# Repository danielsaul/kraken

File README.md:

The Kraken
==========
Poseidon Ocean Drifter Project  
http://poseidon.sgsphysics.co.uk

Tracker
http://track.poseidon.sgsphysics.co.uk/

Various Authors

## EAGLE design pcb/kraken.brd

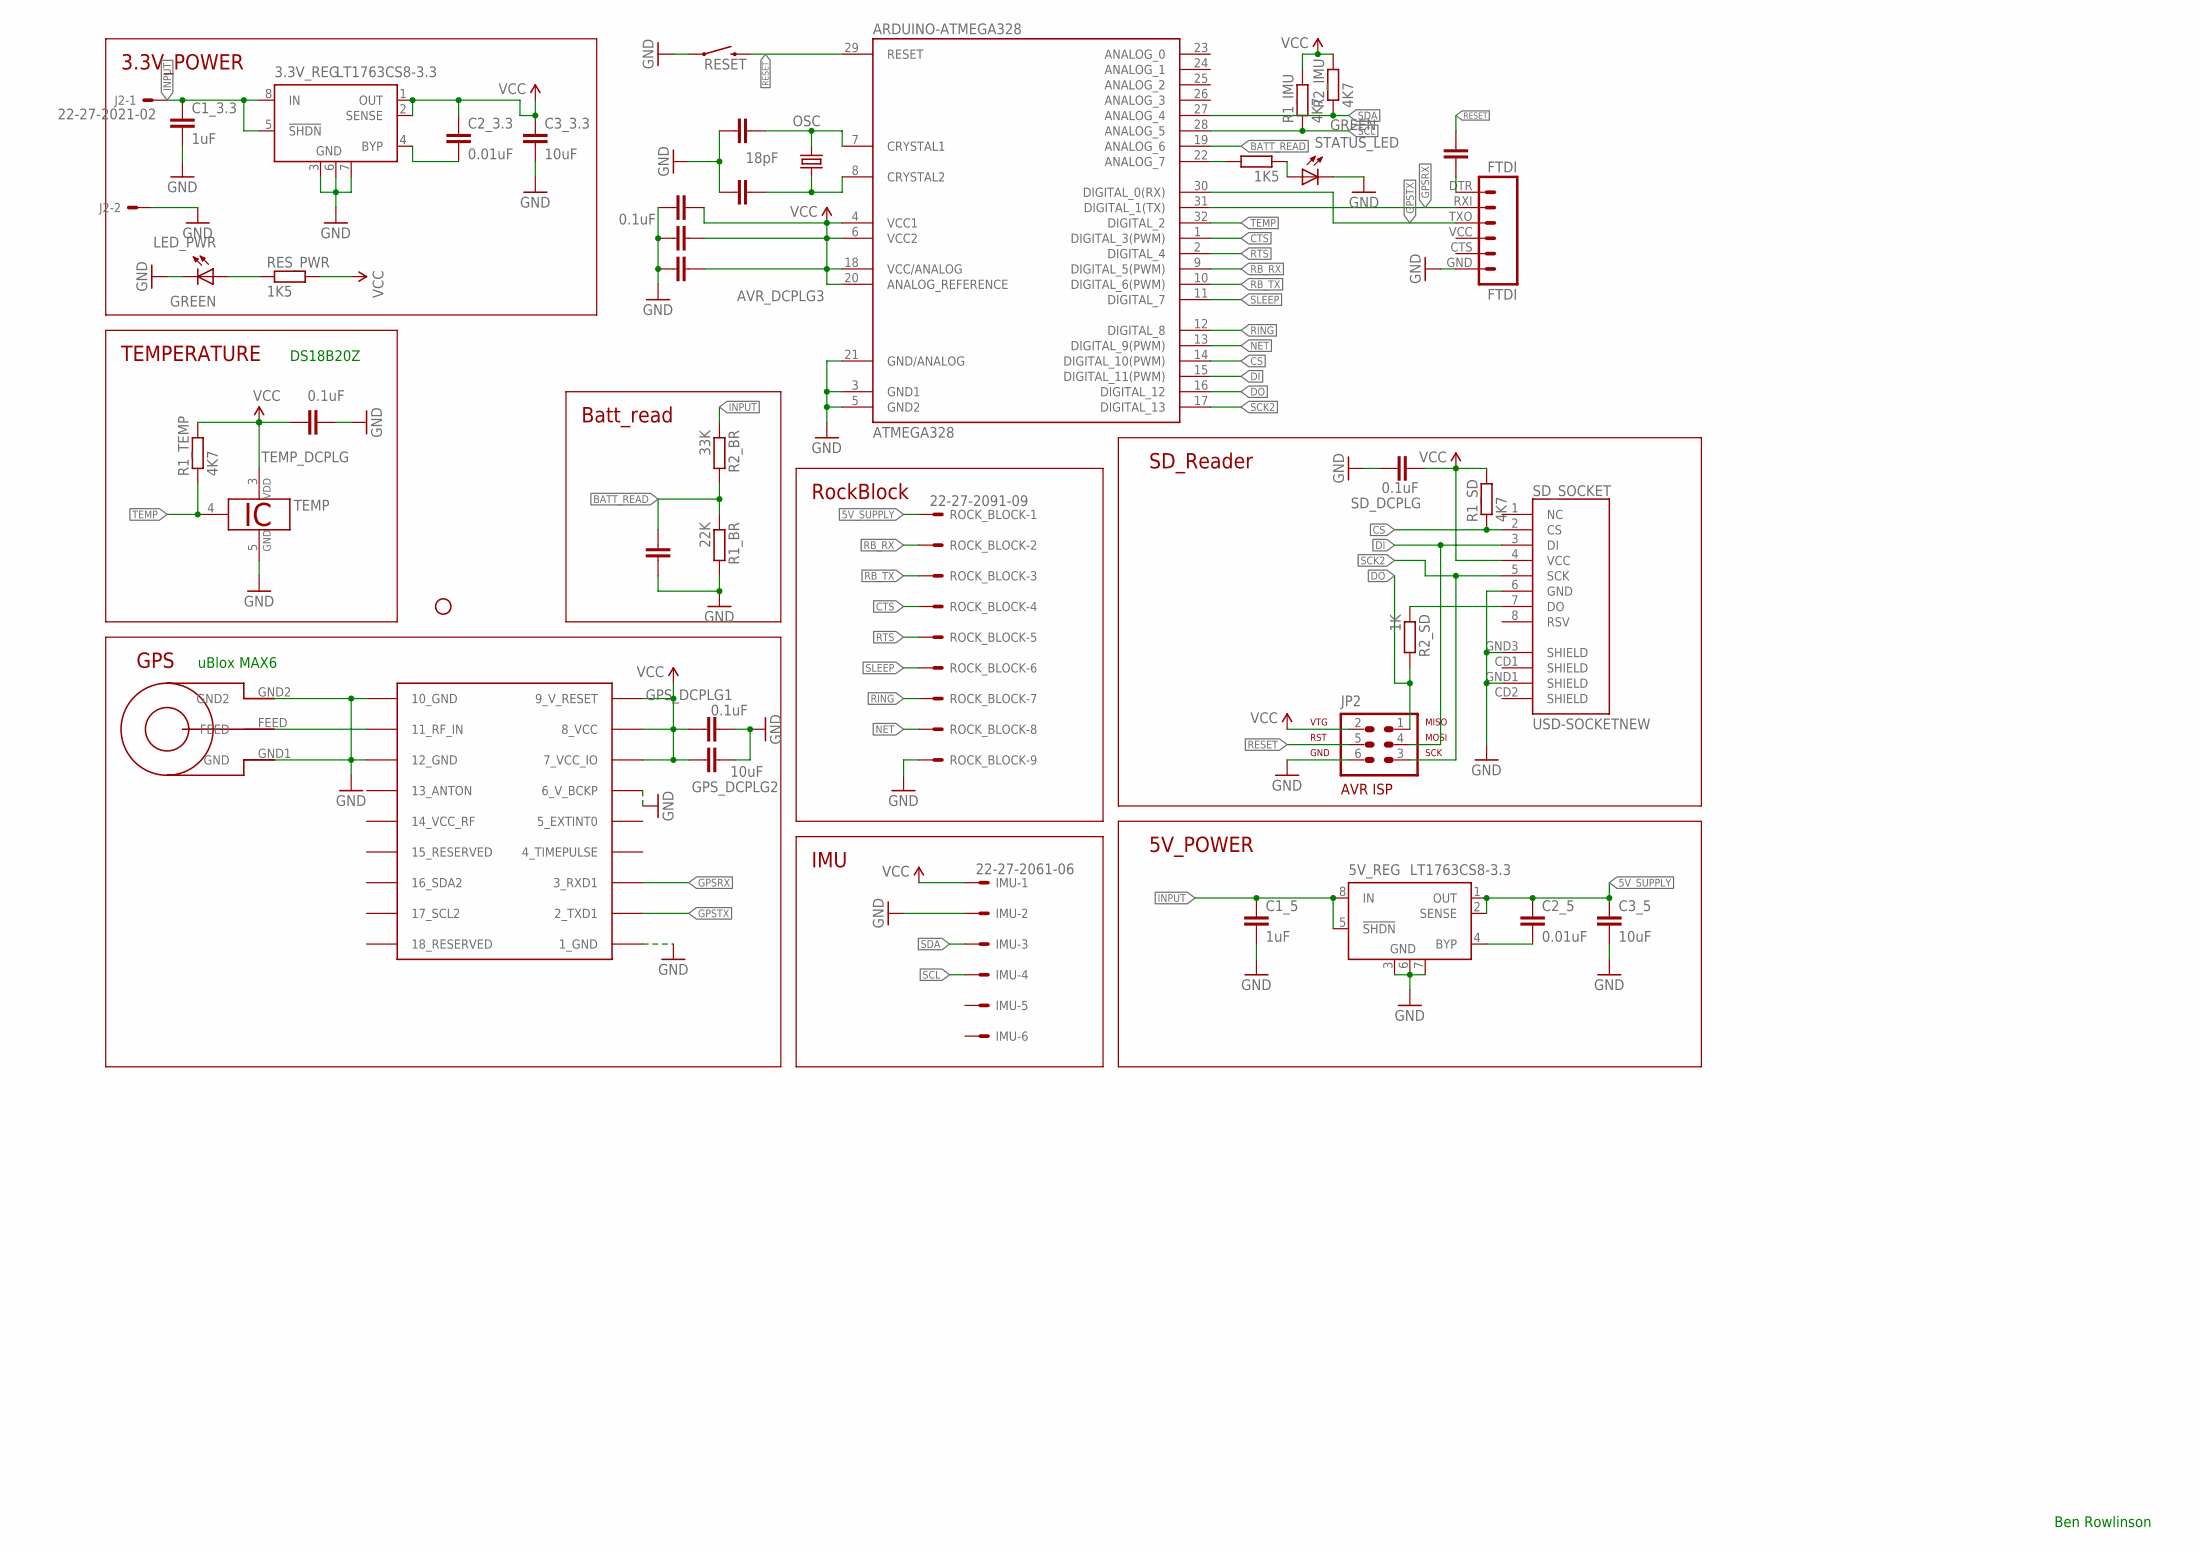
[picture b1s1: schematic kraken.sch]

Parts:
3.3V_REG, 5V_REG: LT1763CS8-3.3; SOIC8
ARDUINO-ATMEGA328: ATMEGA328; TQFP32-08
AVR_DCPLG1, AVR_DCPLG2, AVR_DCPLG3: 0.1uF; 0805
C1_3.3, C1_5: 1uF; 0805
C1_BR: 0.1uF; 0805
C1_OSC, C2_OSC: 18pF; 0805
C2_3.3, C2_5: 0.01uF; 0805
C3_3.3, C3_5: 10uF; 0805
FTDI: FTDI; FTDI_BASIC
FTDI_DCPLG: 0.1uF; 0805
GPS_DCPLG1: 0.1uF; 0805
GPS_DCPLG2: 10uF; 0805
IMU: 22-27-2061-06; 6410-06
J2: 22-27-2021-02; 6410-02
JP1: STAND-OFF
JP2: AVR-ISP-6
LED_PWR: GREEN; CHIPLED_0603
OSC: 16MHz; CRYSTAL-SMD-5X3
R1_BR: 22K; R0805
R1_IMU, R1_SD, R1_TEMP, R2_IMU: 4K7; R0805
R2_BR: 33K; R0805
R2_SD: 1K; R0805
RESET: SW-MOMENTARY-SMD; TACTILE-SWITCH-1101NE
RES_PWR: 1K5; R0805
ROCK_BLOCK: 22-27-2091-09; 6410-09
R_STATUS: 1K5; R0805
SD_DCPLG: 0.1uF; 0805
SD_SOCKET: USD-SOCKETNEW; MICRO-SD-SOCKET-PP
STATUS_LED: GREEN; CHIPLED_0603
TEMP: DS18B20Z; SO08
TEMP_DCPLG: 0.1uF; 0805
U$1: UBLOX_MAX-6
U$2: SARANTEL-SR1202

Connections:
5V_SUPPLY: 5V_REG.1 (OUT), 5V_REG.2 (SENSE), C2_5.1, C3_5.1, ROCK_BLOCK.1
BATT_READ: ARDUINO-ATMEGA328.19 (ANALOG_6), C1_BR.2, R1_BR.1, R2_BR.2
CS: ARDUINO-ATMEGA328.14 (DIGITAL_10(PWM)), R1_SD.1, SD_SOCKET.2 (CS)
CTS: ARDUINO-ATMEGA328.1 (DIGITAL_3(PWM)), ROCK_BLOCK.4
DI: ARDUINO-ATMEGA328.15 (DIGITAL_11(PWM)), JP2.4, SD_SOCKET.3 (DI)
DO: ARDUINO-ATMEGA328.16 (DIGITAL_12), JP2.1, R2_SD.2
GND: 3.3V_REG.3 (GND), 3.3V_REG.6 (GND), 3.3V_REG.7 (GND), 5V_REG.3 (GND), 5V_REG.6 (GND), 5V_REG.7 (GND), ARDUINO-ATMEGA328.3 (GND1), ARDUINO-ATMEGA328.5 (GND2), ARDUINO-ATMEGA328.21 (GND/ANALOG), AVR_DCPLG1.1, AVR_DCPLG2.1, AVR_DCPLG3.1, C1_3.3.2, C1_5.2, C1_BR.1, C1_OSC.1, C2_OSC.1, C3_3.3.2, C3_5.2, FTDI.GND (6), GPS_DCPLG1.2, GPS_DCPLG2.2, IMU.2, J2.2, JP2.6, LED_PWR.C, R1_BR.2, RESET.P$1 (1), ROCK_BLOCK.9, SD_DCPLG.2, SD_SOCKET.6 (GND), SD_SOCKET.GND1 (SHIELD), SD_SOCKET.GND3 (SHIELD), STATUS_LED.C, TEMP.5 (GND), TEMP_DCPLG.1, U$1.1_GND, U$1.6_V_BCKP, U$1.10_GND, U$1.12_GND, U$2.GND1 (GND), U$2.GND2
GPSRX: ARDUINO-ATMEGA328.31 (DIGITAL_1(TX)), FTDI.RXI (2), U$1.3_RXD1
GPSTX: ARDUINO-ATMEGA328.30 (DIGITAL_0(RX)), FTDI.TXO (3), U$1.2_TXD1
INPUT: 3.3V_REG.5 (!SHDN), 3.3V_REG.8 (IN), 5V_REG.5 (!SHDN), 5V_REG.8 (IN), C1_3.3.1, C1_5.1, J2.1, R2_BR.1
unnamed: R_STATUS.1, STATUS_LED.A
unnamed: R2_SD.1, SD_SOCKET.7 (DO)
unnamed: LED_PWR.A, RES_PWR.1
unnamed: ARDUINO-ATMEGA328.22 (ANALOG_7), R_STATUS.2
unnamed: ARDUINO-ATMEGA328.8 (CRYSTAL2), C2_OSC.2, OSC.1
unnamed: ARDUINO-ATMEGA328.7 (CRYSTAL1), C1_OSC.2, OSC.3 (2)
unnamed: 3.3V_REG.4 (BYP), C2_3.3.2
unnamed: U$1.11_RF_IN, U$2.FEED
unnamed: 5V_REG.4 (BYP), C2_5.2
unnamed: FTDI.DTR (1), FTDI_DCPLG.2
NET: ARDUINO-ATMEGA328.13 (DIGITAL_9(PWM)), ROCK_BLOCK.8
RB_RX: ARDUINO-ATMEGA328.9 (DIGITAL_5(PWM)), ROCK_BLOCK.2
RB_TX: ARDUINO-ATMEGA328.10 (DIGITAL_6(PWM)), ROCK_BLOCK.3
RESET: ARDUINO-ATMEGA328.29 (RESET), FTDI_DCPLG.1, JP2.5, RESET.P$2 (2)
RING: ARDUINO-ATMEGA328.12 (DIGITAL_8), ROCK_BLOCK.7
RTS: ARDUINO-ATMEGA328.2 (DIGITAL_4), ROCK_BLOCK.5
SCK2: ARDUINO-ATMEGA328.17 (DIGITAL_13), JP2.3, SD_SOCKET.5 (SCK)
SCL: ARDUINO-ATMEGA328.28 (ANALOG_5), IMU.4, R1_IMU.1
SDA: ARDUINO-ATMEGA328.27 (ANALOG_4), IMU.3, R2_IMU.1
SLEEP: ARDUINO-ATMEGA328.11 (DIGITAL_7), ROCK_BLOCK.6
TEMP: ARDUINO-ATMEGA328.32 (DIGITAL_2), R1_TEMP.1, TEMP.4 (1W)
VCC: 3.3V_REG.1 (OUT), 3.3V_REG.2 (SENSE), ARDUINO-ATMEGA328.4 (VCC1), ARDUINO-ATMEGA328.6 (VCC2), ARDUINO-ATMEGA328.18 (VCC/ANALOG), ARDUINO-ATMEGA328.20 (ANALOG_REFERENCE), AVR_DCPLG1.2, AVR_DCPLG2.2, AVR_DCPLG3.2, C2_3.3.1, C3_3.3.1, GPS_DCPLG1.1, GPS_DCPLG2.1, IMU.1, JP2.2, R1_IMU.2, R1_SD.2, R1_TEMP.2, R2_IMU.2, RES_PWR.2, SD_DCPLG.1, SD_SOCKET.4 (VCC), TEMP.3 (VDD), TEMP_DCPLG.2, U$1.7_VCC_IO, U$1.8_VCC, U$1.9_V_RESET

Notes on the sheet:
3.3V_POWER
TEMPERATURE
Ben Rowlinson
GPS
uBlox MAX6
DS18B20Z
RockBlock
IMU
5V_POWER
SD_Reader
Batt_read

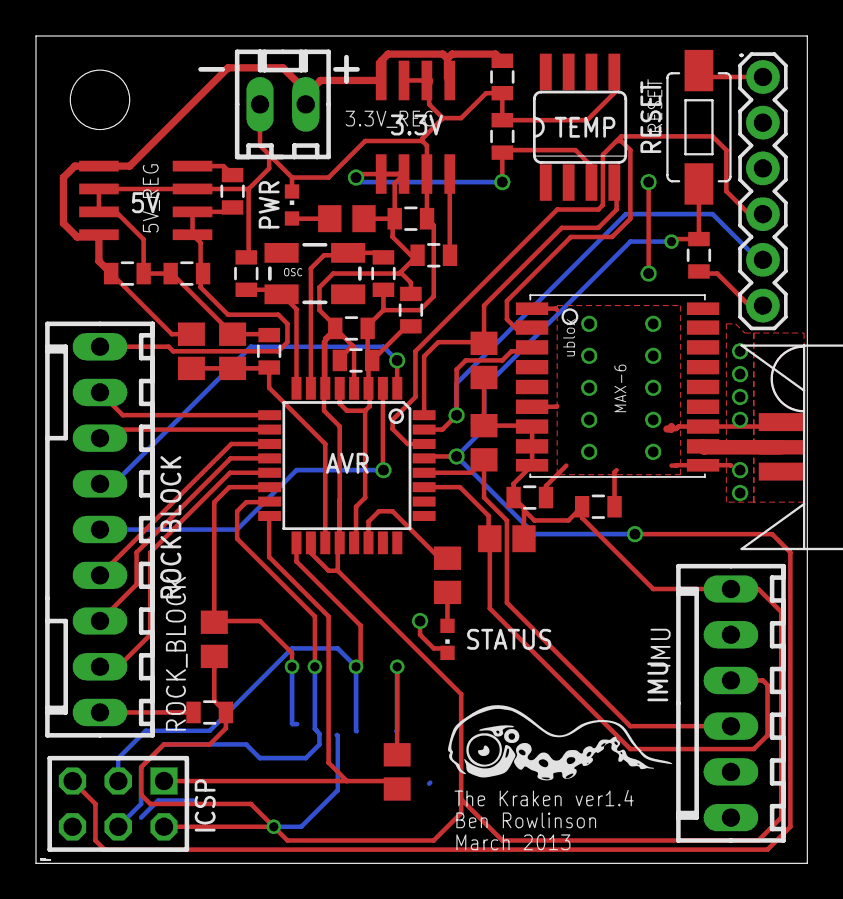
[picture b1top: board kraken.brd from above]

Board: 2 copper layers, 42.7 x 45.8 mm, 43 parts (1 on the bottom side), 32 nets.

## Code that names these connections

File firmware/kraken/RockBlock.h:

/**
  * RockBlock.h
  *
  * Part of the Kraken Ocean Drifter
  * http://poseidon.sgsphysics.co.uk
  *
  * Daniel Saul
  * (C) SGS Poseidon Project 2013
  */

#ifndef ROCKBLOCK_H
#define ROCKBLOCK_H

#include "Arduino.h"
#include <SoftwareSerial.h>
#include "debug.h"
#include <string.h>

const uint8_t RB_RX = 5;     // Serial RX
const uint8_t RB_TX = 6;     // Serial TX
const uint8_t RB_CTS = 3;    
const uint8_t RB_RTS = 4;
const uint8_t RB_SLEEP = 7;  // POWER ON/OFF 
const uint8_t RB_RING = 8;   // RING INDICATOR
const uint8_t RB_NET = 9;    // NETWORK AVAILABLE

const uint8_t minimumSignalRequired = 2;
const uint16_t maxTelemetryLength = 340;
const uint16_t responseLost = 30000;


void rockblock_init();
void rockblock_on();
void rockblock_off();

bool initiateSession();
bool loadMessage(unsigned char *msg, int length);
int readMessage(unsigned char *msg, int maxLength);

void parseSBDIX();

bool sendCommandandExpectPrefix(const char * command, const char * response, unsigned long timeout);
void sendCommand(const char * command);
bool expectResponse(const char * response, unsigned long timeout);

bool receiveCmdCRLF(unsigned long timeout);
void clearReceivedCmd();

int checkSignal();
bool isSatAvailable();

bool messageSent();
int messagesToReceive();
int messagesWaitingOnNetwork();
bool messageAvailableToRead();

#endif

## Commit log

2013-03-23 Added schematic and pcb
2013-03-23 First code commit
2013-03-23 Changed duplicate file structure
2013-03-23 The very very very start of a program.
2013-03-25 Added libs
2013-03-25 Not much
2013-03-26 Stuff at school
2013-03-26 stuff
2013-03-27 Minibus & stuffs
2013-03-27 got gps stuff working
2013-03-27 only goes into power save if has lock
2013-03-27 only goes into power save if has lock - fixed for seamode
2013-03-28 Tidied GPS code
2013-03-28 Changed rockblock timeout
2013-03-28 Tidied setup()
2013-03-28 Added and edited files from Apex. Temperature, Counter, Battery etc.
2013-03-28 Started SD card
2013-03-30 tidy code, collect GPS, temp, battery data, send via iridium
2013-03-30 added IMU code
2013-03-30 changed sample rate
2013-03-30 sample rate
2013-03-30 cut down ram usage, change sample rate
2013-03-31 put imu into sleep mode
2013-03-31 power saving and fixing rockblock bugs
2013-03-31 sleep between transmission using watchdog to wake up
2013-03-31 imu data in every nth transmission
2013-03-31 tidy up debug messages
2013-03-31 debug off and interval set to 6 hours
2013-03-31 rockblock init
2013-03-31 rockblock awake for longer
2013-04-01 rockblock retries if no sats
2013-04-01 sleep for shorter time if unsuccessful
2013-04-01 6 hour sleep
2013-04-02 added uptime to transmission
2013-04-02 remove uptime
2013-04-04 turn debug off
2013-04-04 transmit every 30 min for the first day [i don't like last minute firmware changes - :(]
2013-04-21 Revert "turn debug off"
    This reverts commit e652ed92ef84c52d558841d1414abc6c91c7aa60.
2013-04-21 added constant to enable/disable IMU
2013-04-21 added commenting
2013-04-21 turn imu off
2013-04-21 Added Kraken2 temp sensor address
2013-04-22 Remove leftover head stuff
2013-04-22 Transitioning Iridium9602 content to RockBlock
2013-04-22 Remove 5s wait - if it breaks, it's Priyesh's fault
2013-04-22 Nearly finished transferring Iridium9602
2013-04-23 Finish combining Iridium9602 and RockBlock
2013-04-23 It works, it actually works! New RockBlock stuff
2013-04-24 Started sorting uplink commands
2013-04-24 Added functions to get and set IMU en/freq
2013-04-24 Finished commands and added new IMU functions to main loop
2013-04-24 Fixed compile bug
2013-04-24 Don't need to print SBDIX values anymore
2013-04-24 Added {} because Priyesh said to
2013-04-24 Print cmd in hex
2013-04-24 Disabled debug
2013-04-24 Revert "Disabled debug"
    This reverts commit 643f59a989e43e57b380894fabff0e6293d8c796.
2013-04-24 Added uplink command to change counter val
2013-04-24 Revert "Revert "Disabled debug""
    This reverts commit 68d29e2552030a870280bd71b937b1fe62507712.
2013-06-14 Changed uplink variables to use EEPROM

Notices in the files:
parts and their libraries:
SparkFun-Connectors: Licensing: CC v3.0 Share-Alike You are welcome to use this library for commercial purposes.
